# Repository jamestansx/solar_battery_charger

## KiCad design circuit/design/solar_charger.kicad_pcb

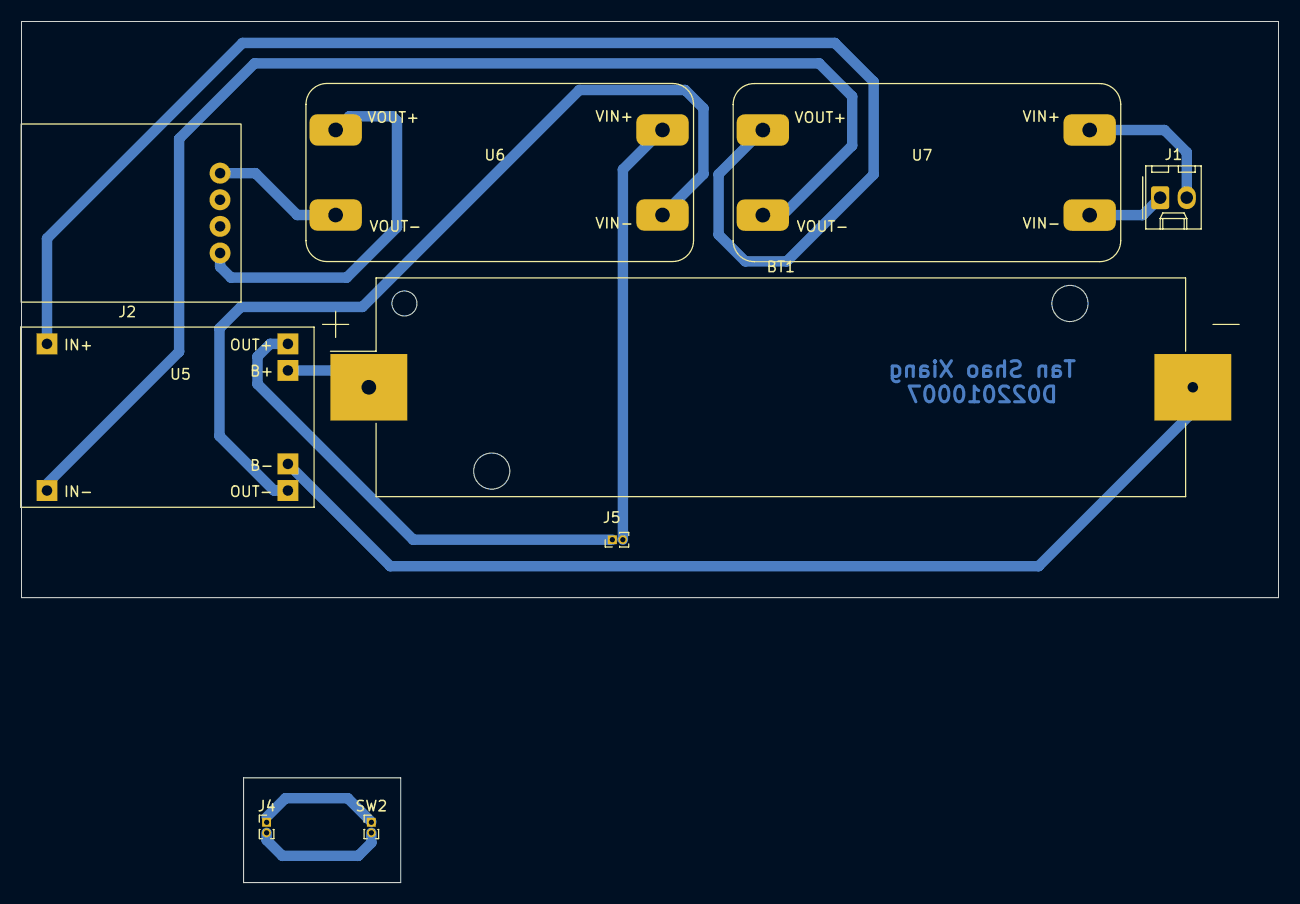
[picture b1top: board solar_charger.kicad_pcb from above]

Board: 2 copper layers, 120.0 x 82.2 mm, 9 parts (0 on the bottom side), 13 nets.

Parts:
BT1: Battery_Cell; BatteryHolder_18650
J1: Screw_Terminal_01x02; Molex_KK-254_AE-6410-02A_1x02_P2.54mm_Vertical
J2: USB_A; USB_A_Breakout
J4, J5: Screw_Terminal_01x02; PinHeader_1x02_P1.00mm_Vertical
SW2: SW_SPST; PinHeader_1x02_P1.00mm_Vertical
U5: TP4056_Breakout; TP4056-Module
U6, U7: MT3608_Breakout; MT3608-Module

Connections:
/SW_SPST: J5.1, U5.5 (OUT^{+})
GND: J1.1, U7.2 (IN^{-})
unnamed: BT1.1 (+), U5.3 (BAT^{+})
unnamed: BT1.2 (-), U5.4 (BAT^{-})
unnamed: J2.1 (VBUS), U6.3 (OUT^{+})
unnamed: J2.4 (GND), U6.4 (OUT^{-})
unnamed: J4.1, SW2.1 (A)
unnamed: J4.2, SW2.2 (B)
unnamed: J5.2, U6.1 (IN^{+})
unnamed: U5.1 (IN), U7.3 (OUT^{+})
unnamed: U5.2 (GND), U7.4 (OUT^{-})
unnamed: U5.6 (OUT^{-}), U6.2 (IN^{-})
V_{IN}: J1.2, U7.1 (IN^{+})

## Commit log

2022-03-16 Ready, set, go!
2022-03-16 Add block diagram
2022-03-16 Move block diagram to docs
2022-03-16 Update Block diagram
2022-03-16 Add project methodology
2022-03-16 Update project methodology
2022-03-16 Add proposal draft
2022-03-17 Added project_methodology_new
2022-03-17 Update project_methodology_new
2022-03-21 Added Operation of block diagram
2022-04-17 Add circuit schematic
2022-05-10 Move circuit design to another folder
2022-05-10 Create case design
2022-07-02 Add gitignore
2022-07-02 Ignore zip file
2022-07-02 Remove unused files
2022-07-02 Update gitignore
2022-07-02 fixup! Update gitignore
2022-07-02 Backup everything
2022-07-10 Reorganise files
2022-07-10 fixup! Backup everything
